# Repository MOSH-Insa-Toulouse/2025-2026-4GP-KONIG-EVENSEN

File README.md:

# LOWTECH FLEX SENSOR
## 2025-2026-4GP-KONIG-EVENSEN

This work is regulated by the Creative Commons Licence CC BY 4.0, for more information 
[follow this link](https://creativecommons.org/licenses/by/4.0/).

---

## Introduction
In this project we sought to create a LowTech flex sensor based on the conduction properties of graphite. LowTech projects consist of developing technological solutions while respecting sobriety, efficiency, durability, maintainability, accessibility, autonomization, empowerment, connectedness and simplification. Hence, it promotes technology which is sustainable both environmentally and socially, as well as uncomplicated and accessible. The following sections will describe the different procedures of the development of the sensor, as well as an evaluation of the performance of the sensor. 

- [The Physics Behind the Graphite Sensor](#the-physics-behind-the-graphite-sensor)
- [Procedure](#procedure)
- [Amplifier Circuit Simulations](#amplifier-circuit-simulations)
- [Printed Circuit Board Design and Development](#printed-circuit-board-design-and-development)
- [Arduino Code](#arduino-code)
- [APK Application Design and Development](#apk-application-design-and-development)
- [Test Setup](#test-setup)
- [Datasheet](#datasheet)
- [Conclusion](#conclusion)

---

## The Physics Behind the Graphite Sensor
This project is based on the research of [Lin et al.](https://www.nature.com/articles/srep03812) on the use of "Pencil Drawn Strain Gauges and Chemiresistors on Paper". They showed that regular commercial pencils deposit fine graphite particles on paper during dry application due to friction. The graphite powder makes up a percolated network which works as a thin conductive film on the paper. This provides an incredibly simple deposition method for generating conductive films in various patterns.
By creating a specific U-shaped pencil trace (see [Datasheet](./GraphiteSensor_Datasheet/Datasheet_Graphite_Flex_Sensor.pdf)), the conductive properties of the graphite network can be used to measure compressive and tensile deflections, and we can therefore employ it as a strain gauge. When the graphite is in compression (inward deflection), the graphite particle network is compressed, creating a more closely connected conductive film, and hence lowering the resistance of the strain gauge. Conversely, tension (outward deflection) increases the resistance of the strain gauge as the distances between the graphite particles increase and disconnect the conduction pathways. The conduction between non-connected graphite particles remains possible due to the tunneling effect in granular systems.

The resistance of the pencil trace can easily be measured, and varies based on the type of pencil used (in this project HB, 3B and 6B). Softer pencils have higher graphite content and therefore show lower resistance.

The application of this principle allows for the production of low-cost, environmentally-friendly and uncomplicated paper-based electronics.

## Procedure
For this project we started off with the design of an amplification circuit based on an operational amplifier of the type LTC1050 for the amplification of the signal from the graphite sensor. Secondly, we designed and developed a printed circuit board for the implementation of the amplification circuit (employing a digital potentiometer of the type MCP41010), an OLED screen, a rotary encoder, a Bluetooth module of the type HC-05 and a commercial flex sensor. All datasheets for the commercial components can be found in the repository [Components_Datasheets](./Components_Datasheets/). The printed circuit board was designed as a shield for an Arduino UNO. Thereafter, we wrote an Arduino IDE script implementing all the components and facilitating the measurement and testing of the graphite flex sensor. Later we designed and developed an APK Application for Android using MIT App Inventor, which allows communication with the Arduino using the Bluetooth module. Finally, we developed a test setup for the quantitative analysis of the graphite sensor's development. All parts of the procedure are further developed in the following part.

## Amplifier Circuit Simulations
Before the conception of the circuit for the realization of the graphite sensor, we performed simulations of the amplifier circuit in order to predict its performance. For this simulation we used the program LTSpice, and the exact files used can be found in the repository [LTSpice_Files](./LTSpice_Files/). The amplifier circuit tested was as follows:

The graphite sensor is simulated by the following circuit:

As the graphite sensor constitutes a very sensitive system, it is extremely susceptible to noise at 50Hz coming from the capacitive coupling to the grid power at 230V, as shown by the Fourier transform of the acquired signal.

The amplifier circuit serves as a low-pass filter with a cutoff frequency at approximately 1.6Hz to reduce the influence of this noise. It also serves to minimize the noise from the other components which will be added to the printed circuit board, such as the clock of the digital circuits and the radio frequency used for the Bluetooth communication. The circuit consists of a passive filter which minimizes high-frequency noise, an active filter of the type LTC1050, and a second passive filter for filtering out the noise coming from the processing of the signal.

During the testing of the circuit's transient response, the dependency on the capacitance C4 became evident. An increased value of the capacitance minimized the influence of noise on the signal, but increased the response time significantly. Contrarily, a decreased value enhanced the response time, but augmented the noise influence. A compromise between the two conflicting properties was made when determining the value of the capacitance.

C4 = 0.1 $\mu$ F

C4 = 1 $\mu$ F

C4 = 10 $\mu$ F

## Printed Circuit Board Design and Development
The design of the printed circuit board (PCB) destined for the use as a shield for an Arduino UNO was done using the program KiCad. Here, diagrams and footprints were made of all the necessary components, and the PCB was designed with the necessary connections between the components and the Arduino UNO. The files fro the diagram and the wiring of the PCB can be found in the repository [KiCad_Files](./KiCad_Files/). The PCB allows the connection between the Arduino UNO and the following components ([link to datasheets](./Components_Datasheets/)).

### Graphite Sensor
The signal of the graphite sensor is connected to the Arduino UNO through the amplifier circuit based on the operational amplifier LTC1050. The digital potentiometer MCP41010 takes part of this circuit and is used to regulate the signal Vadc according to the following formula:

> $R_C = \frac{V_C}{V_A} \cdot R_1 \cdot \left(1 + \frac{R_3}{R_P}\right) - R_1 - R_5$

Where Rc is the resistance of the graphite sensor, Va is the voltage of the output of the amplifier circuit and Rp is the resistance of the digital potentiometer.

The voltage output from the amplifier circuit can be retrieved on the analog pin A0.

### Commercial Flex Sensor
The commercial flex sensor is connected using a resistance of 47kOhms in a voltage divider circuit. The resistance of the flex sensor can be retrieved on the analog pin A1.

### OLED Screen
The OLED Screen used is of the type SBC-OLED01 and uses the SCL (serial clock line) and SDA (serial data line) pins common for the I2C serial communication bus. I2C has a 7-bit address space and transfers data bit by bit between the controller and the target. The SDA and SCL pins correspond to the pin A4 and A5, respectively, on the Arduino UNO.

### Rotary Encoder
A rotary encoder of the type KY-040 is connected using the CLK, DT and SW pins. The SW (switch) and CLK (clock) are connected to respectively the pins D2 and D3 of the Arduino UNO as these permit the use of interruptions, as is generated on CLK when rotating the rotary encoder. The DT (data) pin connects to D4.
Inside the rotary encoder, two switches serve to determine a rotation as they are either both opened or closed in each encoder position. The order in which the switches change state is used to determine the direction of the rotation, as shown by the diagram below:

A capacitor is connected between the ground and the CLK pin in order to stabilize the interrupt signal.

### Bluetooth Module
Bluetooth permits wireless communication between devices, and in this project a Bluetooth module of the type HC-05 is used to establish communication between the Arduino UNO and other devices. It communicates using radio frequencies around 2.4GHz, which is the same as mobile phones and Wi-Fi. This module provides serial communication over the TxD (transmission) and RxD (receiving) pins, connected to the TxD (7) and RxD pins (8) of the Arduino UNO. 

### Printed Circuit Board Development
For the development of the PCB a PDF-file of the PCB design was printed on transparent paper and used as a mask during UV-exposure of a laminate board covered by a thin layer of copper and photo resist. The exposed photo resist is removed using an alkaline solution, and a copper solvent solution bath removes the uncovered copper. Lastly, the hardened photo resist is removed and only the wanted copper traces on the laminate board are left.

Afterwards, holes are drilled and passive components, as well as supports for the active components, are welded to the printed circuit board.

## Arduino Code
After the conception of the PCB, we continued to the development of an Arduino IDE code allowing control of the components. The Arduino code has multiple functionalities interconnecting the electrical components.

The use of the rotary encoder controls a menu on the OLED screen. The menu includes three different modes: "Flex", "Graphite" and "GitHub QR". Clicking the rotary encoder accesses the different modes, and clicking it again returns to the main menu.

**Flex:** 
The Flex mode permits the monitoring of the commercial flex sensor, printing the resistance and the corresponding angle to the serial monitor of Arduino IDE.

**Graphite:**
The Graphite mode permits the monitoring of the LowTech graphite sensor. The first time the graphite mode is activated, a calibration of the digital potentiometer is started, changing its resistance value in order to get a Vadc corresponding to approximately 2.5V (512 bits). When adjusted, the graphite mode prints the resistance of the graphite sensor to the serial monitor of Arduino IDE.

**GitHub QR:**
The GitHub QR mode displays a QR code which links to the GitHub page of this project.

The Arduino code also manages the serial communication over Bluetooth which is used for the transfer of data between the Arduino UNO and an Android device when using the APK Application which will be described in the following section. The full code can be found in the repository [Arduino_Code](./Arduino_Code/).

## APK Application Design and Development
An APK Application for Android has been developed using the program MIT App Inventor. This application can easily be downloaded to any Android device and permits a simple monitoring of the Arduino UNO. The application allows for connecting to a Bluetooth module such as the HC-05. Depending on if the Flex mode or the Graphite mode is activated, the graphs in the application display the current measured resistance and the relative resistance when "Start" is clicked. When "Stop" is clicked the measurement will stop, and if "Start" is then reclicked, the graphs reset and a new measurement starts. The results of a measurement can be shared or saved using the "Share Result" button. It will then be shared as a text file with the format "x1,y1;x2,y2;...". A "Scan QR Code" button permits the scanning of QR codes, such as the one displayed in QR mode, leading directly to the GitHub page of this project. The programming of the application is shown by the blocs in the repository [APK_Application](./APK_Application/).

## Test Setup
For the testing of the performance of the LowTech graphite sensor, we developed a simple test setup based on the principle of a three-point flexural test. We designed a 3D model using TinkerCad and printed it with the help of extremely knowledgeable and helpful representatives of the INSA Toulouse FabLab Fabric'INSA. The STL-files can be found in the repository [TestSetup_Files](./TestSetup_Files/Projet_MOSH.stl).

The test setup enables both tension and compression tests, and can be used for both the commercial flex sensor and the LowTech graphite sensor at the same time. The absolute value of the strain is calculated using the following formula:

> $\epsilon = \frac{6Dd}{L^2}$

where D(mm) is the maximum deflection of the middle of the graphite sensor, d(mm) is the thickness of the paper, and L(mm) is the length between the two supports of the test module.

## Datasheet
Lastly, we created a [datasheet](./GraphiteSensor_Datasheet/Datasheet_Graphite_Flex_Sensor.pdf) for the LowTech graphite flex sensor, of the type Extra Long Special Edition C5462310 (the number corresponding to the CID PubChem Compound Identification of graphite) in a manner corresponding to the commercial flex sensor. Specifications of the properties and performance of the graphite sensor are listed in order to increase the usability of the sensor.

## Conclusion
In order to conclude on the results of this project, we have analyzed the performance of the LowTech graphite sensor compared to a commercial flex sensor. We identified sensitivity as a relevant metric as this determines the smallest measurable difference in strain, the input value. When analyzing the sensitivity of the graphite sensor, we found that the harder pencils showed a higher sensibility (see the [datasheet](./GraphiteSensor_Datasheet/Datasheet_Graphite_Flex_Sensor.pdf) of the graphite sensor). However, when testing the sensitivity of the commercial flex sensor in extension (as it can only be bent in one direction), the sensitivity of the LowTech graphite sensor proved much weaker.

In addition, the reproducibility of the graphite sensor is questionable. The results from the tests show little to no predictability of the results with extreme uncertainty in the resistance response to the application of both tension and compression to the graphite sensor. We estimate that this is partly because of multiple sources of error coming from the hardware and the fabrication of the PCB. With higher accuracy in the fabrication process, a more predictable and reproducible performance might be possible.

Nonetheless, the feasibility and the LowTech aspect of the graphite sensor must be appreciated. This project shows that a well-functioning flex sensor can be fabricated from the simplest materials, particularly a pencil and paper, and with little to no previous experience with the fabrication of integrated circuits. Moreover, easily accessible components and simple processes serve to increase the performance of the graphite sensor noticeably. Even though the weak sensitivity decreases the probability of the graphite sensor becoming industrializable, the graphite sensor represents a technology available for almost everyone. All in all, this project shows that a transition to LowTech solutions makes technology much more accessible and increases its sustainability for both people and the planet.

---

Created by Svea KÖNIG and Maia EVENSEN (4GP INSA Toulouse)

For support, contact konig@insa-toulouse.fr or evensen@insa-toulouse.fr

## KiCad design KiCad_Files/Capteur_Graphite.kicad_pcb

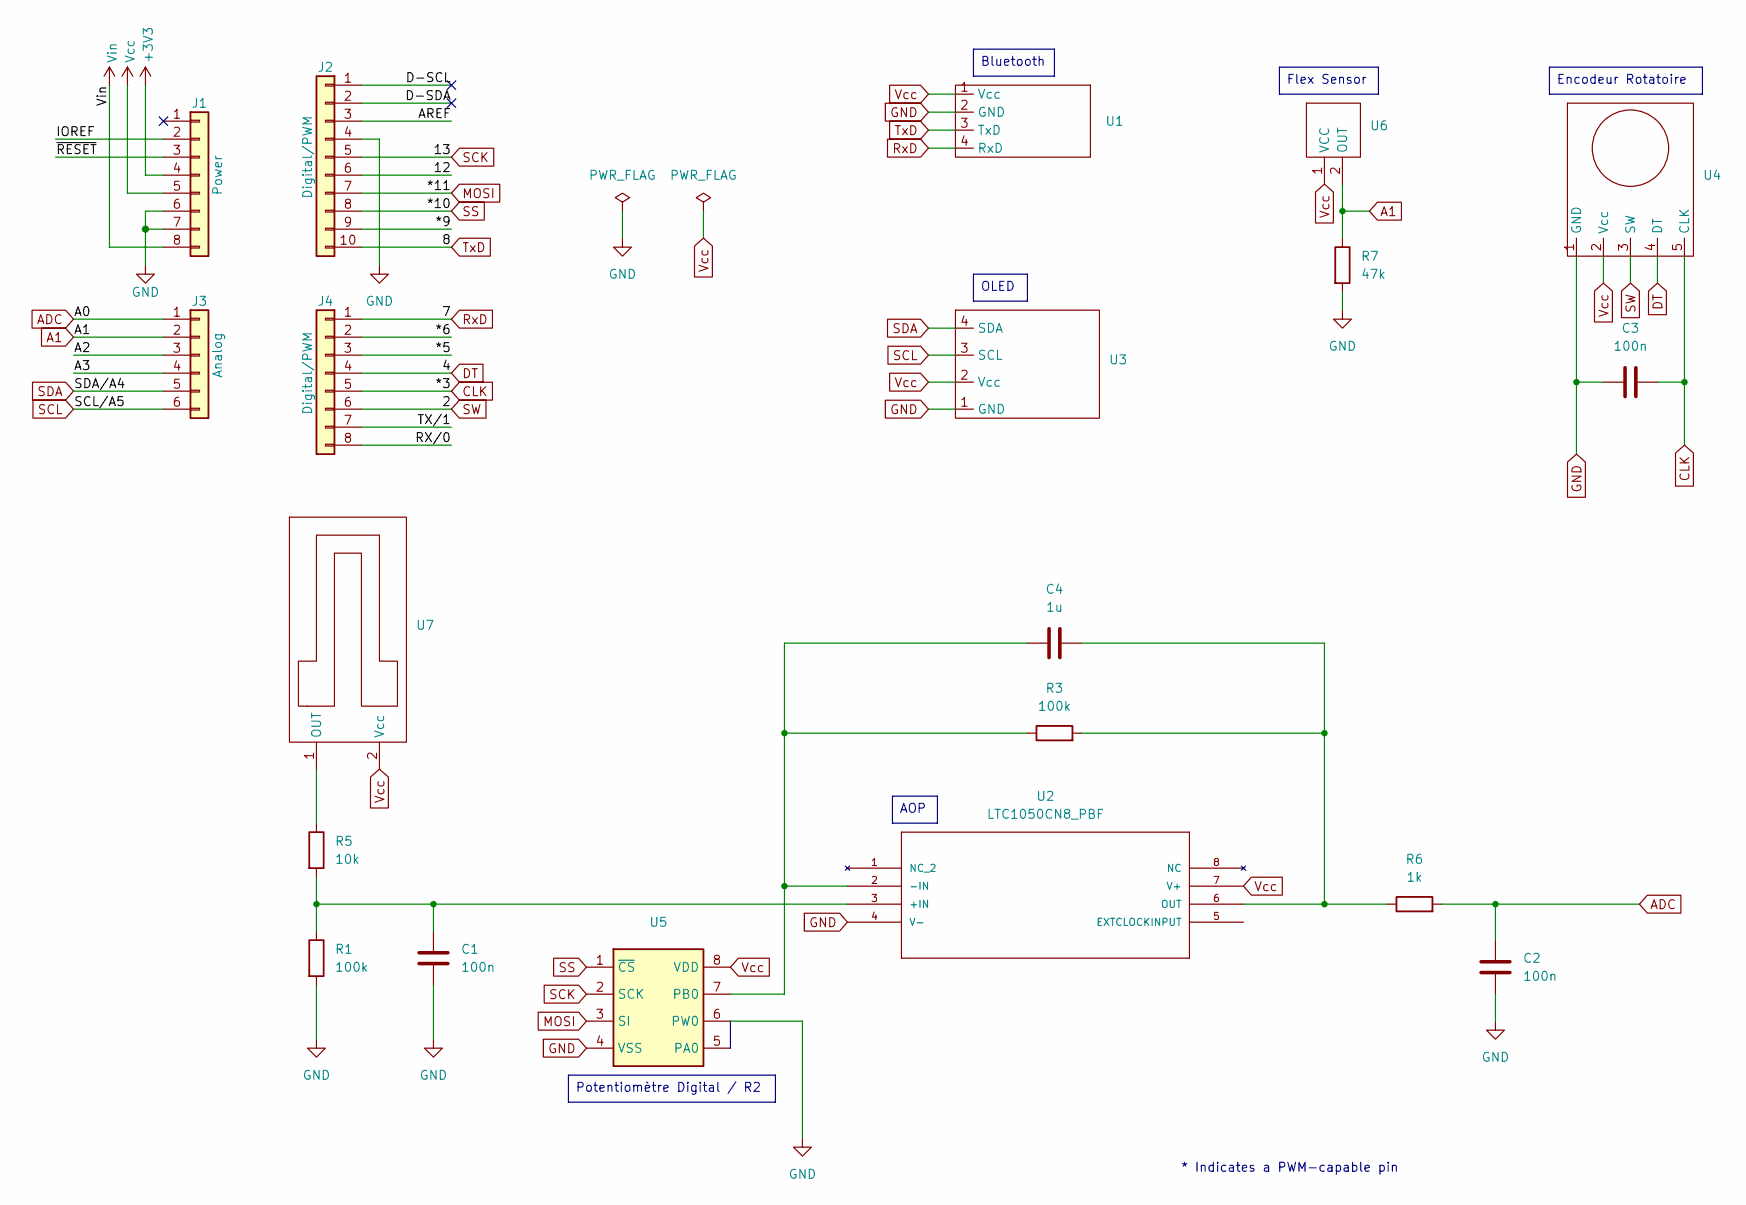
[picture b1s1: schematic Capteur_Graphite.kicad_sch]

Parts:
C1, C2, C3: 100n; Capacite
C4: 1u; Capacite
J1: Power; PinSocket_1x08_P2.54mm_Vertical
J2: Digital/PWM; PinSocket_1x10_P2.54mm_Vertical
J3: Analog; PinSocket_1x06_P2.54mm_Vertical
J4: Digital/PWM; PinSocket_1x08_P2.54mm_Vertical
R1, R3: 100k; Resistance
R5: 10k; Resistance
R6: 1k; Resistance
R7: 47k; Resistance
U1: BLUETOOTH_HC05
U2: LTC1050CN8_PBF; LTC1050
U3: OLED
U4: Encodeur_Rotatoire
U5: MCP41010
U6: Flex_Sensor
U7: Graphite_Flex_Sensor

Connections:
+3V3: J1.4
/12: J2.6
/*5: J4.3
/*6: J4.2
/*9: J2.9
/A2: J3.3
/A3: J3.4
/AREF: J2.3
/D-SCL: J2.1
/D-SDA: J2.2
/IOREF: J1.2
/RX/0: J4.8
/TX/1: J4.7
/~RESET: J1.3
A1: J3.2, R7.1, U6.2 (OUT)
ADC: C2.1, J3.1, R6.2
CLK: C3.2, J4.5, U4.5 (CLK)
DT: J4.4, U4.4 (DT)
GND: C1.2, C2.2, C3.1, J1.6, J1.7, J2.4, R1.2, R7.2, U1.2 (GND), U2.4 (V-), U3.1 (GND), U4.1 (GND), U5.4 (VSS), U5.5 (PA0), U5.6 (PW0)
MOSI: J2.7, U5.3 (SI)
unnamed: C1.1, R1.1, R5.2, U2.3 (+IN)
unnamed: C4.1, R3.1, U2.2 (-IN), U5.7 (PB0)
unnamed: C4.2, R3.2, R6.1, U2.6 (OUT)
unnamed: R5.1, U7.1 (OUT)
RxD: J4.1, U1.4 (RxD)
SCK: J2.5, U5.2 (SCK)
SCL: J3.6, U3.3 (SCL)
SDA: J3.5, U3.4 (SDA)
SS: J2.8, U5.1 (~CS)
SW: J4.6, U4.3 (SW)
TxD: J2.10, U1.3 (TxD)
Vcc: J1.5, U1.1 (Vcc), U2.7 (V+), U3.2 (Vcc), U4.2 (Vcc), U5.8 (VDD), U6.1 (VCC), U7.2 (Vcc)
Vin: J1.8

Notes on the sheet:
* Indicates a PWM-capable pin
Flex Sensor
OLED
Potentiomètre Digital / R2
AOP
Bluetooth
Encodeur Rotatoire

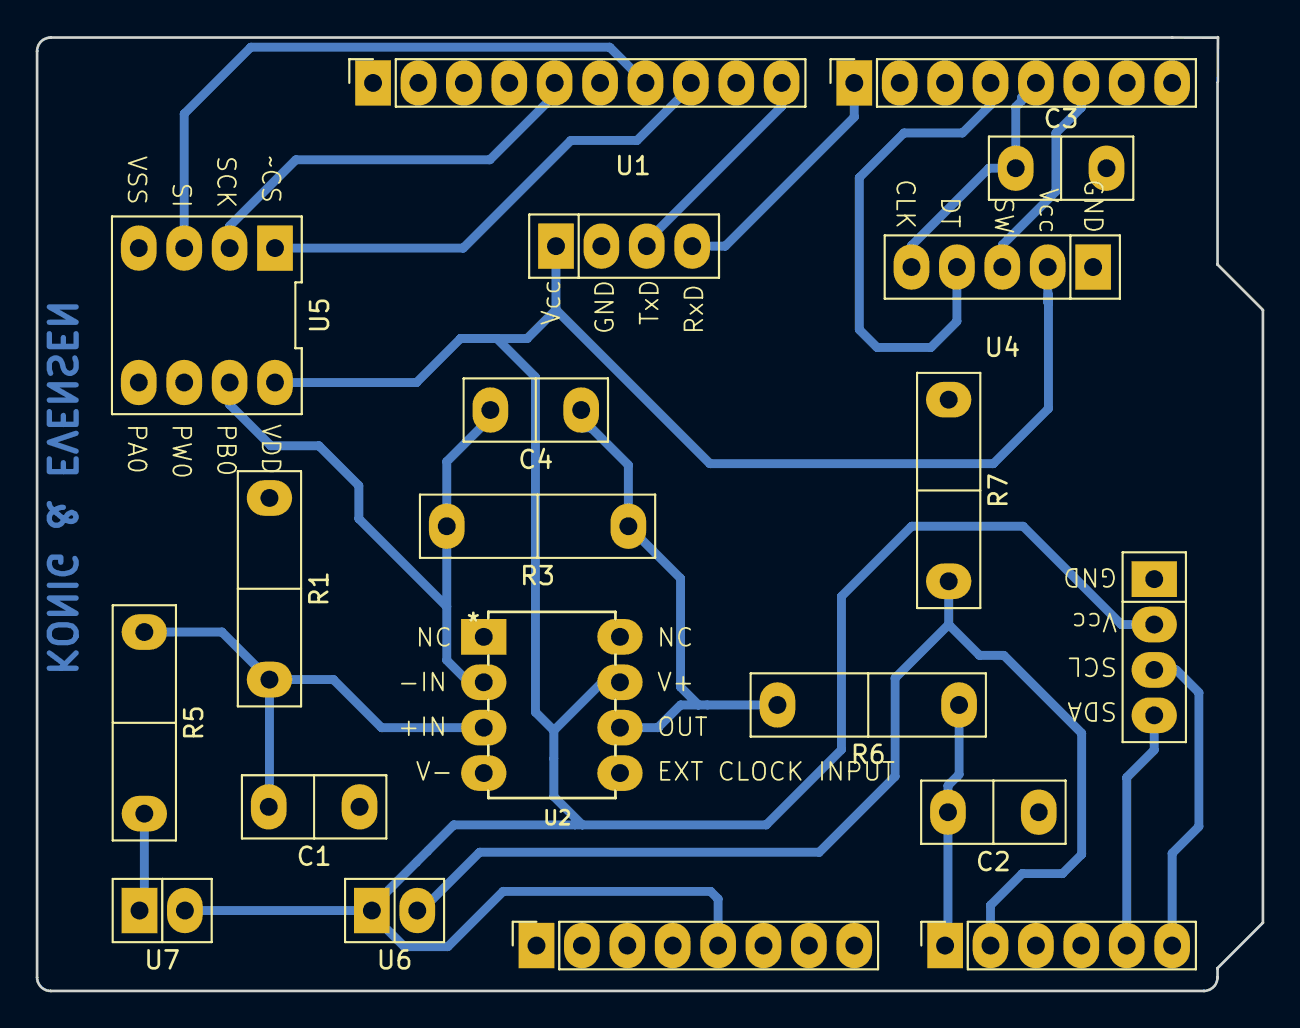
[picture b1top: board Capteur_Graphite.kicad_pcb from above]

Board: 2 copper layers, 68.6 x 53.4 mm, 20 parts (0 on the bottom side), 18 nets.

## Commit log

2026-02-10 endringer README
2026-02-10 personalized license
2026-02-10 test commit
2026-02-10 liten test
2026-02-10 added KiCad file
2026-04-05 STL file of 3D print for flex test
2026-04-06 Added KiCad files
2026-04-06 Added LTSpice files
2026-04-12 Added files for the current Arduino programs
2026-04-12 Clean-ups in the repositories and writing of the README.md
2026-04-13 Added datasheets
2026-04-14 Added library QR.h
2026-04-15 Updated Full_code.ino
2026-04-16 Added comments and wiring descriptions to Full_code.ino
2026-04-16 Updated Bluetooth code
2026-04-16 Added photos to README.md
2026-04-16 Svea: added the Datasheet for the sensor as a pdf
2026-04-16 Added photos of the KiCad and LTspice
2026-04-16 edited README.md
2026-04-16 Edited folders
2026-04-16 Added photo of PCB 3D model
2026-04-16 Maia : Small touchups
2026-04-16 Updated README.md to include Datasheet
2026-04-16 Resized photos
2026-04-16 Edited formula for Rc
2026-04-16 Changed formula formatting
2026-04-16 Changed size of photos
2026-04-16 Added conclusion to the README.md and changed the formating of the formulas
2026-04-16 Added ¨ to König, sorry Svea
2026-04-16 CleanUps in the photos folder and added a repository for the APK Application
2026-04-16 Removed Test KiCad
2026-04-16 Updated content list in README.md
2026-04-16 Grammar checking of the README.md file
2026-04-16 CleanUps of the entire branch
2026-04-16 Grammar checks
